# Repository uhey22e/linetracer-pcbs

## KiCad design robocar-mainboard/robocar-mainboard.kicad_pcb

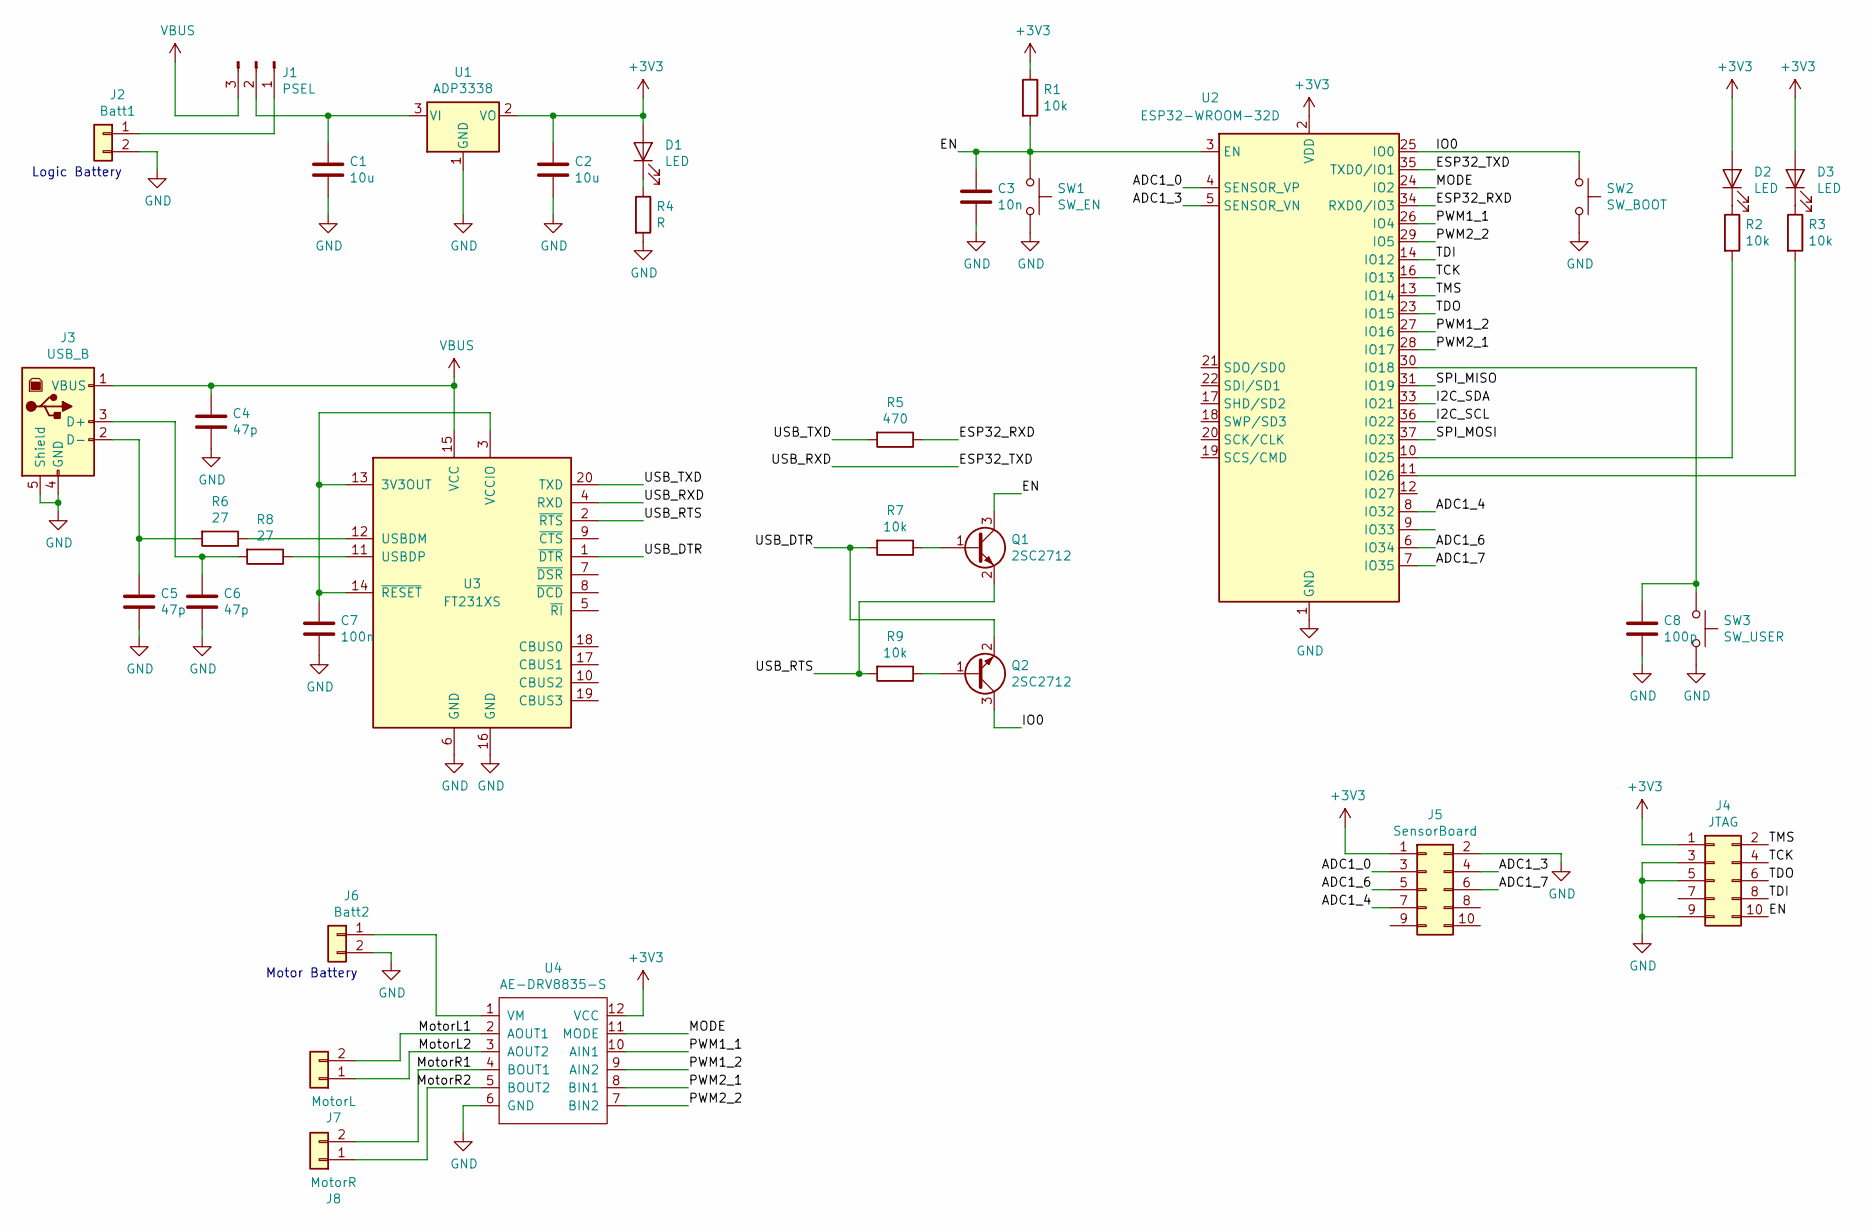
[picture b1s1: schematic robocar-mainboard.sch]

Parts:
C1, C2: 10u; C_1210_3225Metric_Pad1.42x2.65mm_HandSolder
C3: 10n; C_0603_1608Metric_Pad1.05x0.95mm_HandSolder
C4, C5, C6: 47p; C_0603_1608Metric_Pad1.05x0.95mm_HandSolder
C7: 100n; C_0603_1608Metric_Pad1.05x0.95mm_HandSolder
C8: 100p; C_0603_1608Metric_Pad1.05x0.95mm_HandSolder
D1, D2, D3: LED; LED_D3.0mm
J1: PSEL; PinHeader_1x03_P2.54mm_Vertical
J2: Batt1; TerminalBlock_bornier-2_P5.08mm
J3: USB_B; USB_B_OST_USB-B1HSxx_Horizontal
J4: JTAG; PinHeader_2x05_P2.54mm_Vertical
J5: SensorBoard; PinHeader_2x05_P2.54mm_Vertical
J6: Batt2; TerminalBlock_bornier-2_P5.08mm
J7: MotorL; TerminalBlock_bornier-2_P5.08mm
J8: MotorR; TerminalBlock_bornier-2_P5.08mm
Q1, Q2: 2SC2712; SC-59
R1, R2, R3, R7, R9: 10k; R_0603_1608Metric_Pad1.05x0.95mm_HandSolder
R4: R; R_0603_1608Metric_Pad1.05x0.95mm_HandSolder
R5: 470; R_0603_1608Metric_Pad1.05x0.95mm_HandSolder
R6, R8: 27; R_0603_1608Metric_Pad1.05x0.95mm_HandSolder
SW1: SW_EN; SW_PUSH_6mm_H5mm
SW2: SW_BOOT; SW_PUSH_6mm_H5mm
SW3: SW_USER; SW_PUSH_6mm_H5mm
U1: ADP3338; SOT-223-3_TabPin2
U2: ESP32-WROOM-32D; ESP32-WROOM-32
U3: FT231XS; SSOP-20_3.9x8.7mm_P0.635mm
U4: AE-DRV8835-S; DIP-12_W7.62mm_Socket_LongPads

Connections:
+3V3: C2.1, D1.2 (A), D2.2 (A), D3.2 (A), J4.1, J5.1, R1.1, U1.2 (VO), U2.2 (VDD), U4.12 (VCC)
/ADC1_0: J5.3, U2.4 (SENSOR_VP)
/ADC1_3: J5.4, U2.5 (SENSOR_VN)
/ADC1_4: J5.7, U2.8 (IO32)
/ADC1_6: J5.5, U2.6 (IO34)
/ADC1_7: J5.6, U2.7 (IO35)
/ESP32_RXD: R5.1, U2.34 (RXD0/IO3)
/ESP32_TXD: U2.35 (TXD0/IO1), U3.4 (RXD)
/I2C_SCL: U2.36 (IO22)
/I2C_SDA: U2.33 (IO21)
/IO0: Q2.3 (C), SW2.1, U2.25 (IO0)
/MODE: U2.24 (IO2), U4.11 (MODE)
/MotorL1: J7.2, U4.2 (AOUT1)
/MotorL2: J7.1, U4.3 (AOUT2)
/MotorR1: J8.2, U4.4 (BOUT1)
/MotorR2: J8.1, U4.5 (BOUT2)
/PWM1_1: U2.26 (IO4), U4.10 (AIN1)
/PWM1_2: U2.27 (IO16), U4.9 (AIN2)
/PWM2_1: U2.28 (IO17), U4.8 (BIN1)
/PWM2_2: U2.29 (IO5), U4.7 (BIN2)
/SPI_MISO: U2.31 (IO19)
/SPI_MOSI: U2.37 (IO23)
/TCK: J4.4, U2.16 (IO13)
/TDI: J4.8, U2.14 (IO12)
/TDO: J4.6, U2.23 (IO15)
/TMS: J4.2, U2.13 (IO14)
/USB_DTR: Q2.2 (E), R7.2, U3.1 (~DTR)
/USB_RTS: Q1.2 (E), R9.2, U3.2 (~RTS)
/USB_TXD: R5.2, U3.20 (TXD)
unnamed: C1.1, J1.2, U1.3 (VI)
unnamed: C5.1, J3.2 (D-), R6.2
unnamed: C6.1, J3.3 (D+), R8.2
unnamed: C7.1, U3.3 (VCCIO), U3.13 (3V3OUT), U3.14 (~RESET)
unnamed: C8.1, SW3.1, U2.30 (IO18)
unnamed: D1.1 (K), R4.1
unnamed: D2.1 (K), R2.1
unnamed: D3.1 (K), R3.1
unnamed: J1.1, J2.1
unnamed: J6.1, U4.1 (VM)
unnamed: Q1.1 (B), R7.1
unnamed: Q2.1 (B), R9.1
unnamed: R2.2, U2.10 (IO25)
unnamed: R3.2, U2.11 (IO26)
unnamed: R6.1, U3.12 (USBDM)
unnamed: R8.1, U3.11 (USBDP)
VBUS: C4.1, J1.3, J3.1 (VBUS), U3.15 (VCC)

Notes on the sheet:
Logic Battery
Motor Battery

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
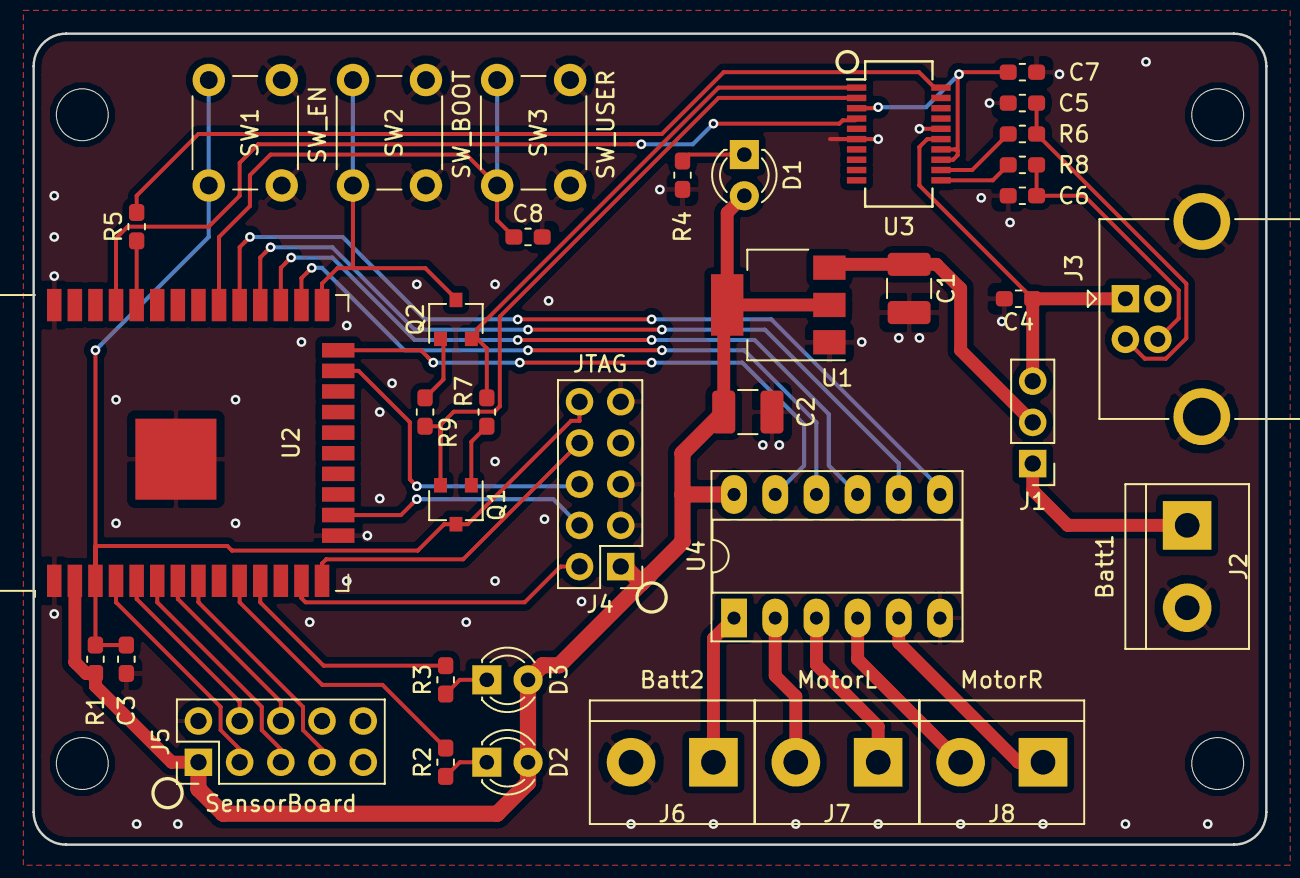
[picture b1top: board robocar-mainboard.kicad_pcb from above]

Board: 2 copper layers, 76.0 x 50.0 mm, 41 parts (0 on the bottom side), 44 nets.

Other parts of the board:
REF1, REF2, REF3, REF4: MountingHole_3.2mm_M3

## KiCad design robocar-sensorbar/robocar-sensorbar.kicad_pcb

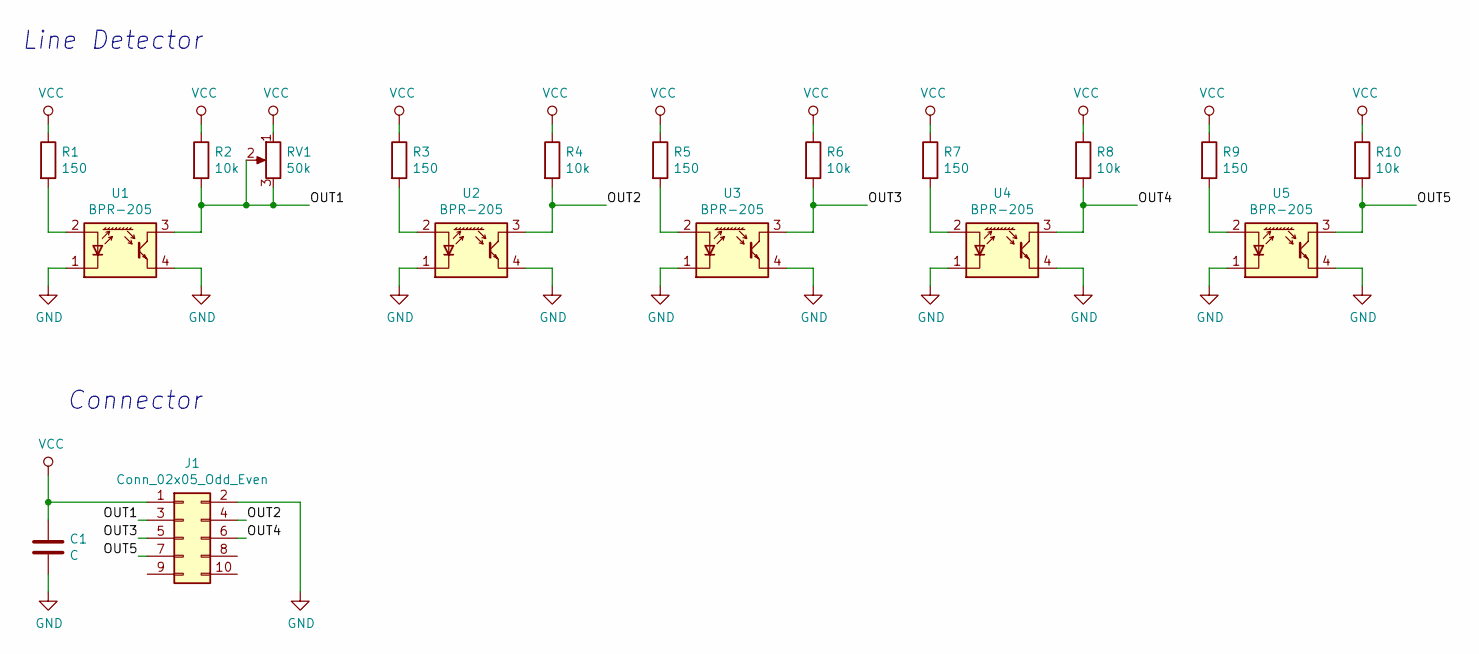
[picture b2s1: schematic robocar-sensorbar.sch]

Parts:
C1: C; C_0603_HandSoldering
J1: Conn_02x05_Odd_Even; Pin_Header_Straight_2x05_Pitch2.54mm
R1, R3, R5, R7, R9: 150; R_0603_HandSoldering
R2, R4, R6, R8, R10: 10k; R_0603_HandSoldering
RV1: 50k; Potentiometer_Trimmer_Copal_CT-6EP
U1, U2, U3, U4, U5: BPR-205; LBR-127HD

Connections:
/OUT1: J1.3, R2.2, RV1.2, RV1.3, U1.3 (C)
/OUT2: J1.4, R4.2, U2.3 (C)
/OUT3: J1.5, R6.2, U3.3 (C)
/OUT4: J1.6, R8.2, U4.3 (C)
/OUT5: J1.7, R10.2, U5.3 (C)
GND: C1.1, J1.2, U1.1 (K), U1.4 (E), U2.1 (K), U2.4 (E), U3.1 (K), U3.4 (E), U4.1 (K), U4.4 (E), U5.1 (K), U5.4 (E)
unnamed: R1.2, U1.2 (A)
unnamed: R3.2, U2.2 (A)
unnamed: R5.2, U3.2 (A)
unnamed: R7.2, U4.2 (A)
unnamed: R9.2, U5.2 (A)
VCC: C1.2, J1.1, R1.1, R2.1, R3.1, R4.1, R5.1, R6.1, R7.1, R8.1, R9.1, R10.1, RV1.1

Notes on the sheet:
Line Detector
Connector

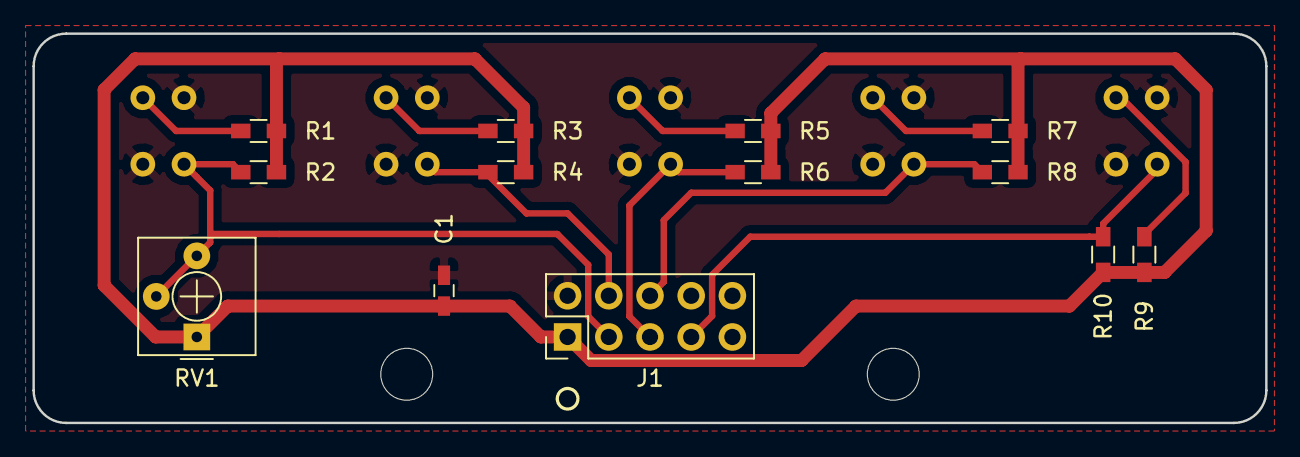
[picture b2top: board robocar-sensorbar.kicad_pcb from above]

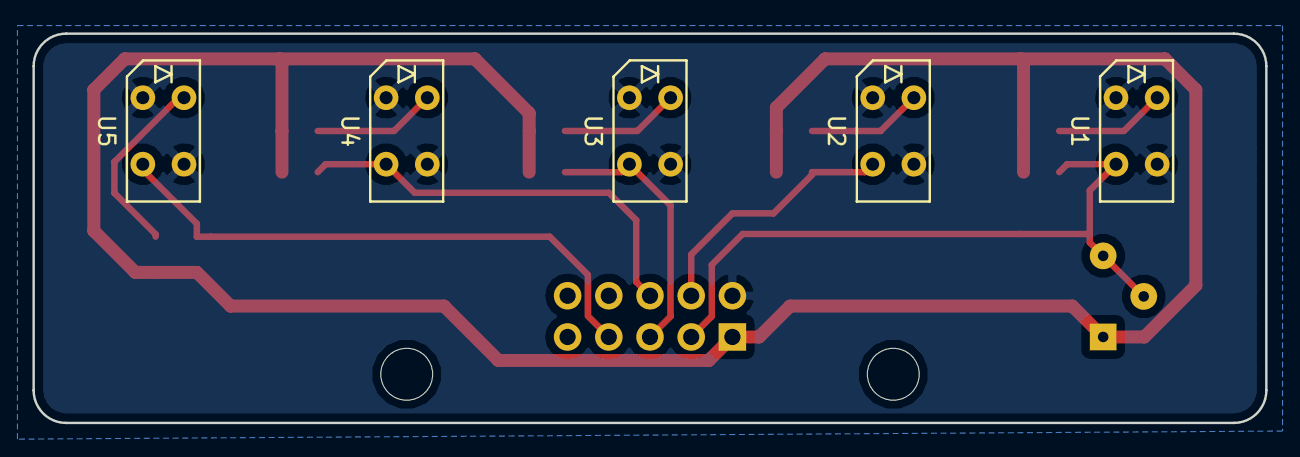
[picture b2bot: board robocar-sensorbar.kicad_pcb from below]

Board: 2 copper layers, 76.0 x 24.0 mm, 18 parts (5 on the bottom side), 12 nets.

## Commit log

2019-08-26 add kicad projects
2019-09-16 回路図の見栄えをよく
2019-09-29 諸々整理
